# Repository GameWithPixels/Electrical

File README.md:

View this project on [CADLAB.io](https://cadlab.io/project/24232). 

# Electrical

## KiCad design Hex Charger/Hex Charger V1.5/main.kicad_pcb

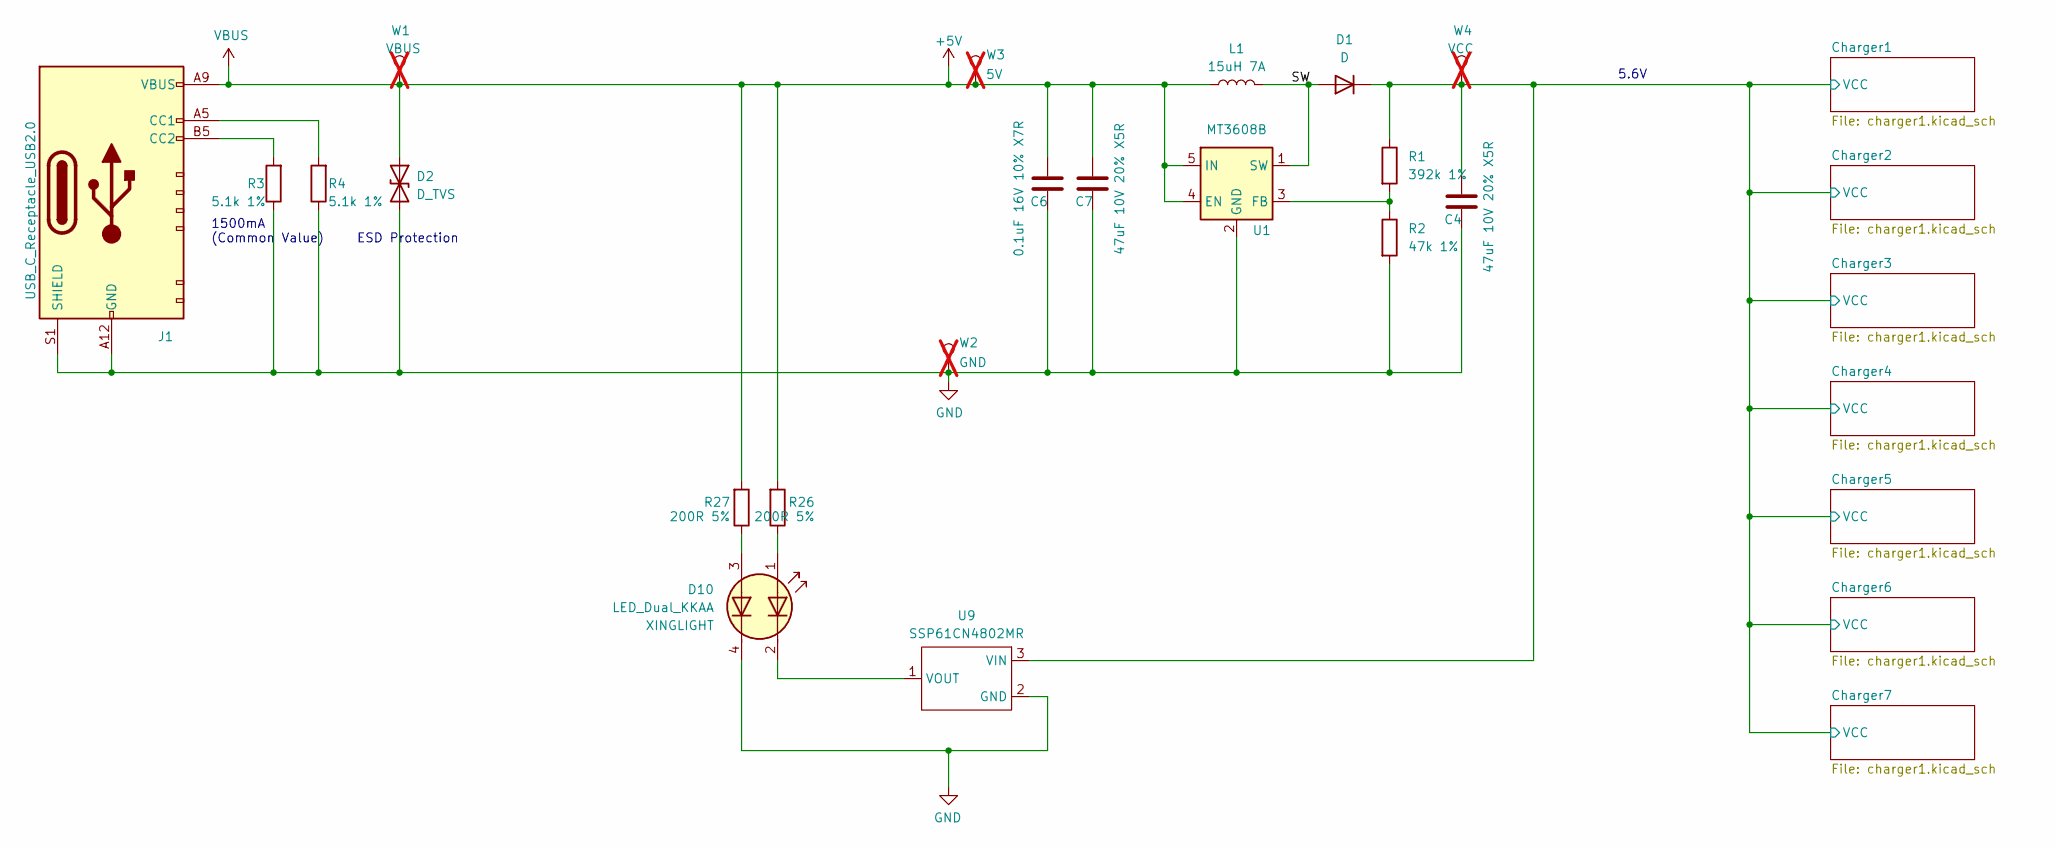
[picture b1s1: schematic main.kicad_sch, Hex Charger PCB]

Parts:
C4, C7: 47uF 10V 20% X5R; C_1206_3216Metric; Part Number CGA1206X5R476M100NT
C6: 0.1uF 16V 10% X7R; C_0603_1608Metric; Part Number CGA0603X7R104K500JT
D1: D; SMAF; Part Number SS54F; LCSC Part # C908671
D2: D_TVS; DFN; Part Number LXES1UTAA1-157; LCSC Part # C5210979
D10: LED_Dual_KKAA; XL-3210SURUGC; Part Number XL-3210SURUGC; LCSC Part # C965883
J1: USB_C_Receptacle_USB2.0; USB-C-SMD_10P-P1.00-L6.8-W8.9; Part Number TYPE-C-31-M-17; LCSC Part # C283540
L1: 15uH 7A; L_Sunlord_MWSA1005S; Part Number MS1050-150M; LCSC Part # C18337490
R1: 392k 1%; R_0402_1005Metric; Part Number 0402WGF3923TCE
R2: 47k 1%; R_0402_1005Metric; Part Number 0402WGF4702TCE
R3, R4: 5.1k 1%; R_0402_1005Metric; Part Number 0402WGF5101TCE; LCSC Part # C25905
R26, R27: 200R 5%; R_0402_1005Metric; Part Number 0402WGF2000TCE; LCSC Part # C25087
U1: MT3608B; SOT-23-6; Part Number MT3608B; LCSC Part # C19189893
U9: SSP61CN4802MR; SOT-23; Part Number HT7050S; LCSC Part # C2842953
W1: VBUS; TestPoint_1.5x1.5_Drill0.9mm; not fitted
W2: GND; TestPoint_1.5x1.5_Drill0.9mm; not fitted
W3: 5V; TestPoint_1.5x1.5_Drill0.9mm; not fitted
W4: VCC; TestPoint_1.5x1.5_Drill0.9mm; not fitted

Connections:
+5V: C6.1, C7.1, D2.1 (A1), J1.A9 (VBUS), J1.B9 (VBUS), L1.1, R26.2, R27.2, U1.4 (EN), U1.5 (IN), W1.1, W3.1
/Charger1/VCC: C4.1, D1.1 (K), R1.1, U9.3 (VIN), W4.1; also elsewhere on the board
/SW: D1.2 (A), L1.2, U1.1 (SW)
GND: C4.2, C6.2, C7.2, D2.2 (A2), D10.4 (K2), J1.A12 (GND), J1.B12 (GND), J1.S1 (SHIELD), R2.2, R3.1, R4.1, U1.2 (GND), U9.2 (GND), W2.1; also elsewhere on the board
unnamed: D10.1 (A1), R26.1
unnamed: D10.3 (A2), R27.1
unnamed: D10.2 (K1), U9.1 (VOUT)
unnamed: J1.A5 (CC1), R4.2
unnamed: J1.B5 (CC2), R3.2
unnamed: R1.2, R2.1, U1.3 (FB)

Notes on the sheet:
1500mA (Common Value)
5.6V
ESD Protection

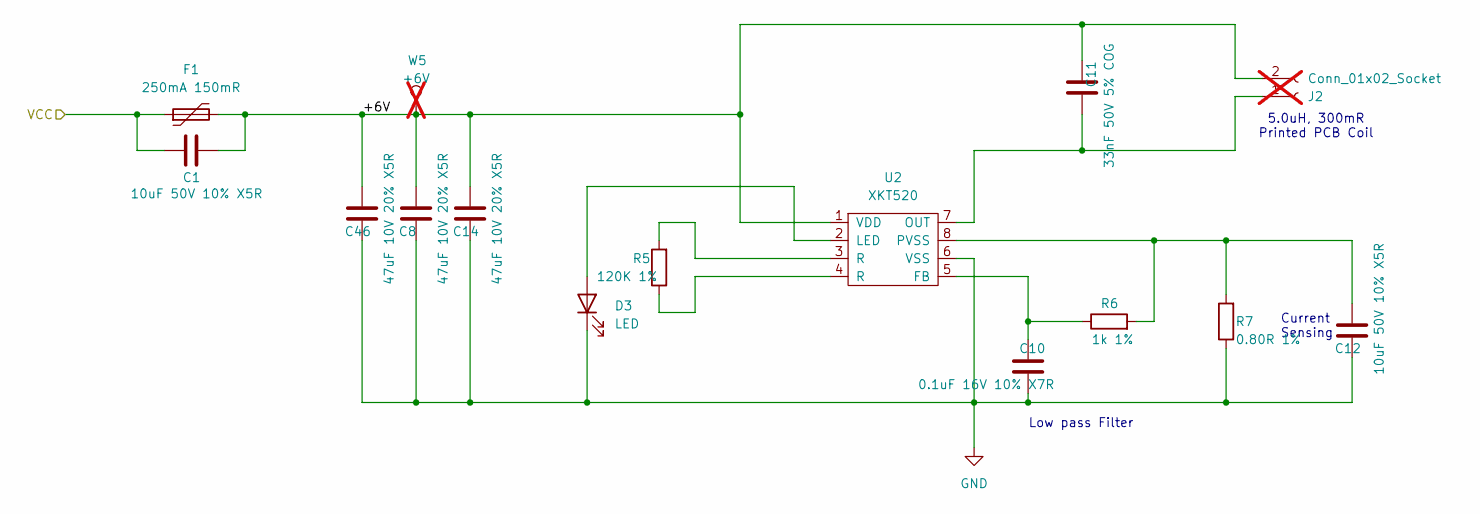
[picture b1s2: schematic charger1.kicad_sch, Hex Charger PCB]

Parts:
C1, C12: 10uF 50V 10% X5R; C_0805_2012Metric; Part Number CGA0805X5R106K250MT
C8, C14, C46: 47uF 10V 20% X5R; C_1206_3216Metric; Part Number CGA1206X5R476M100NT
C10: 0.1uF 16V 10% X7R; C_0603_1608Metric; Part Number CGA0603X7R104K500JT
C11: 33nF 50V 5% COG; C_1206_3216Metric; Part Number GRM3195C1H333JA01D; LCSC Part # C97930
D3: LED; LED_0603_1608Metric; Part Number LTST-C191KRKT; LCSC Part # C125099
F1: 250mA 150mR; Fuse_1206_3216Metric; Part Number BSMD1206-025-33V; LCSC Part # C2977524
J2: Conn_01x02_Socket; COIL_25_6_11T_0750_0255; not fitted
R5: 120K 1%; R_0402_1005Metric; Part Number 0402WGF1203TCE; LCSC Part # C25750
R6: 1k 1%; R_0402_1005Metric; Part Number 0402WGF1001TCE; LCSC Part # C11702
R7: 0.80R 1%; R_1206_3216Metric; Part Number 1206W4F800LT5E
U2: XKT520; SOIC-8_3.9x4.9mm_P1.27mm; Part Number 520
W5: +6V; TestPoint_1.5x1.5_Drill0.9mm; not fitted

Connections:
/Charger1/+6V: C1.1, C8.1, C11.2, C14.1, C46.1, F1.2, J2.2, U2.1 (VDD), W5.1
/Charger1/VCC: C1.2, F1.1; also elsewhere on the board
GND: C8.2, C10.1, C12.2, C14.2, C46.2, D3.1 (K), R7.1, U2.6 (VSS); also elsewhere on the board
unnamed: D3.2 (A), U2.2 (LED)
unnamed: C11.1, J2.1, U2.7 (OUT)
unnamed: R5.1, U2.4 (R)
unnamed: R5.2, U2.3 (R)
unnamed: C10.2, R6.1, U2.5 (FB)
unnamed: C12.1, R6.2, R7.2, U2.8 (PVSS)

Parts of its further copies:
C2, C3, C5, C17, C26, C27, C32, C37, C42, C43, C44, C45: 10uF 50V 10% X5R; C_0805_2012Metric; Part Number CGA0805X5R106K250MT
C13, C18, C19, C21, C28, C33, C34, C38, C47, C48, C49, C50, C51, C52, C53, C55, C57, C59: 47uF 10V 20% X5R; C_1206_3216Metric; Part Number CGA1206X5R476M100NT
C15, C22, C23, C30, C35, C40: 0.1uF 16V 10% X7R; C_0603_1608Metric; Part Number CGA0603X7R104K500JT
C16, C24, C25, C31, C36, C41: 33nF 50V 5% COG; C_1206_3216Metric; Part Number GRM3195C1H333JA01D; LCSC Part # C97930
D4, D5, D6, D7, D8, D9: LED; LED_0603_1608Metric; Part Number LTST-C191KRKT; LCSC Part # C125099
F2, F3, F4, F5, F6, F7: 250mA 150mR; Fuse_1206_3216Metric; Part Number BSMD1206-025-33V; LCSC Part # C2977524
J3, J4, J5, J6, J7, J8: Conn_01x02_Socket; COIL_25_6_11T_0750_0255; not fitted
R8, R11, R12, R17, R20, R23: 120K 1%; R_0402_1005Metric; Part Number 0402WGF1203TCE; LCSC Part # C25750
R9, R13, R14, R18, R21, R24: 1k 1%; R_0402_1005Metric; Part Number 0402WGF1001TCE; LCSC Part # C11702
R10, R15, R16, R19, R22, R25: 0.80R 1%; R_1206_3216Metric; Part Number 1206W4F800LT5E
U3, U4, U5, U6, U7, U8: XKT520; SOIC-8_3.9x4.9mm_P1.27mm; Part Number 520
W6, W7, W8, W9, W10, W11: +6V; TestPoint_1.5x1.5_Drill0.9mm; not fitted

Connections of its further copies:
/Charger1/VCC: C2.2, C3.2, C5.2, C43.2, C44.2, C45.2, F2.1, F3.1, F4.1, F5.1, F6.1, F7.1; also elsewhere on the board
/Charger2/+6V: C2.1, C13.1, C16.2, C21.1, C47.1, F2.2, J3.2, U3.1 (VDD), W6.1
/Charger3/+6V: C3.1, C18.1, C24.2, C34.1, C48.1, F3.2, J4.2, U4.1 (VDD), W7.1
/Charger4/+6V: C5.1, C19.1, C25.2, C49.1, C53.1, F4.2, J5.2, U5.1 (VDD), W8.1
/Charger5/+6V: C28.1, C31.2, C43.1, C50.1, C55.1, F5.2, J6.2, U6.1 (VDD), W9.1
/Charger6/+6V: C33.1, C36.2, C44.1, C51.1, C57.1, F6.2, J7.2, U7.1 (VDD), W10.1
/Charger7/+6V: C38.1, C41.2, C45.1, C52.1, C59.1, F7.2, J8.2, U8.1 (VDD), W11.1
GND: C13.2, C15.1, C17.2, C18.2, C19.2, C21.2, C22.1, C23.1, C26.2, C27.2, C28.2, C30.1, C32.2, C33.2, C34.2, C35.1, C37.2, C38.2, C40.1, C42.2, C47.2, C48.2, C49.2, C50.2, C51.2, C52.2, C53.2, C55.2, C57.2, C59.2, D4.1 (K), D5.1 (K), D6.1 (K), D7.1 (K), D8.1 (K), D9.1 (K), R10.1, R15.1, R16.1, R19.1, R22.1, R25.1, U3.6 (VSS), U4.6 (VSS), U5.6 (VSS), U6.6 (VSS), U7.6 (VSS), U8.6 (VSS); also elsewhere on the board
unnamed: D4.2 (A), U3.2 (LED)
unnamed: D5.2 (A), U4.2 (LED)
unnamed: D6.2 (A), U5.2 (LED)
unnamed: D7.2 (A), U6.2 (LED)
unnamed: D8.2 (A), U7.2 (LED)
unnamed: D9.2 (A), U8.2 (LED)
unnamed: C16.1, J3.1, U3.7 (OUT)
unnamed: C24.1, J4.1, U4.7 (OUT)
unnamed: C25.1, J5.1, U5.7 (OUT)
unnamed: C31.1, J6.1, U6.7 (OUT)
unnamed: C36.1, J7.1, U7.7 (OUT)
unnamed: C41.1, J8.1, U8.7 (OUT)
unnamed: R8.1, U3.4 (R)
unnamed: R8.2, U3.3 (R)
unnamed: R11.1, U4.4 (R)
unnamed: R11.2, U4.3 (R)
unnamed: R12.1, U5.4 (R)
unnamed: R12.2, U5.3 (R)
unnamed: R17.1, U6.4 (R)
unnamed: R17.2, U6.3 (R)
unnamed: R20.1, U7.4 (R)
unnamed: R20.2, U7.3 (R)
unnamed: R23.1, U8.4 (R)
unnamed: R23.2, U8.3 (R)
unnamed: C15.2, R9.1, U3.5 (FB)
unnamed: C17.1, R9.2, R10.2, U3.8 (PVSS)
unnamed: C22.2, R13.1, U4.5 (FB)
unnamed: C26.1, R13.2, R15.2, U4.8 (PVSS)
unnamed: C23.2, R14.1, U5.5 (FB)
unnamed: C27.1, R14.2, R16.2, U5.8 (PVSS)
unnamed: C30.2, R18.1, U6.5 (FB)
unnamed: C32.1, R18.2, R19.2, U6.8 (PVSS)
unnamed: C35.2, R21.1, U7.5 (FB)
unnamed: C37.1, R21.2, R22.2, U7.8 (PVSS)
unnamed: C40.2, R24.1, U8.5 (FB)
unnamed: C42.1, R24.2, R25.2, U8.8 (PVSS)

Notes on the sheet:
5.0uH, 300mR Printed PCB Coil
Current Sensing
Low pass Filter

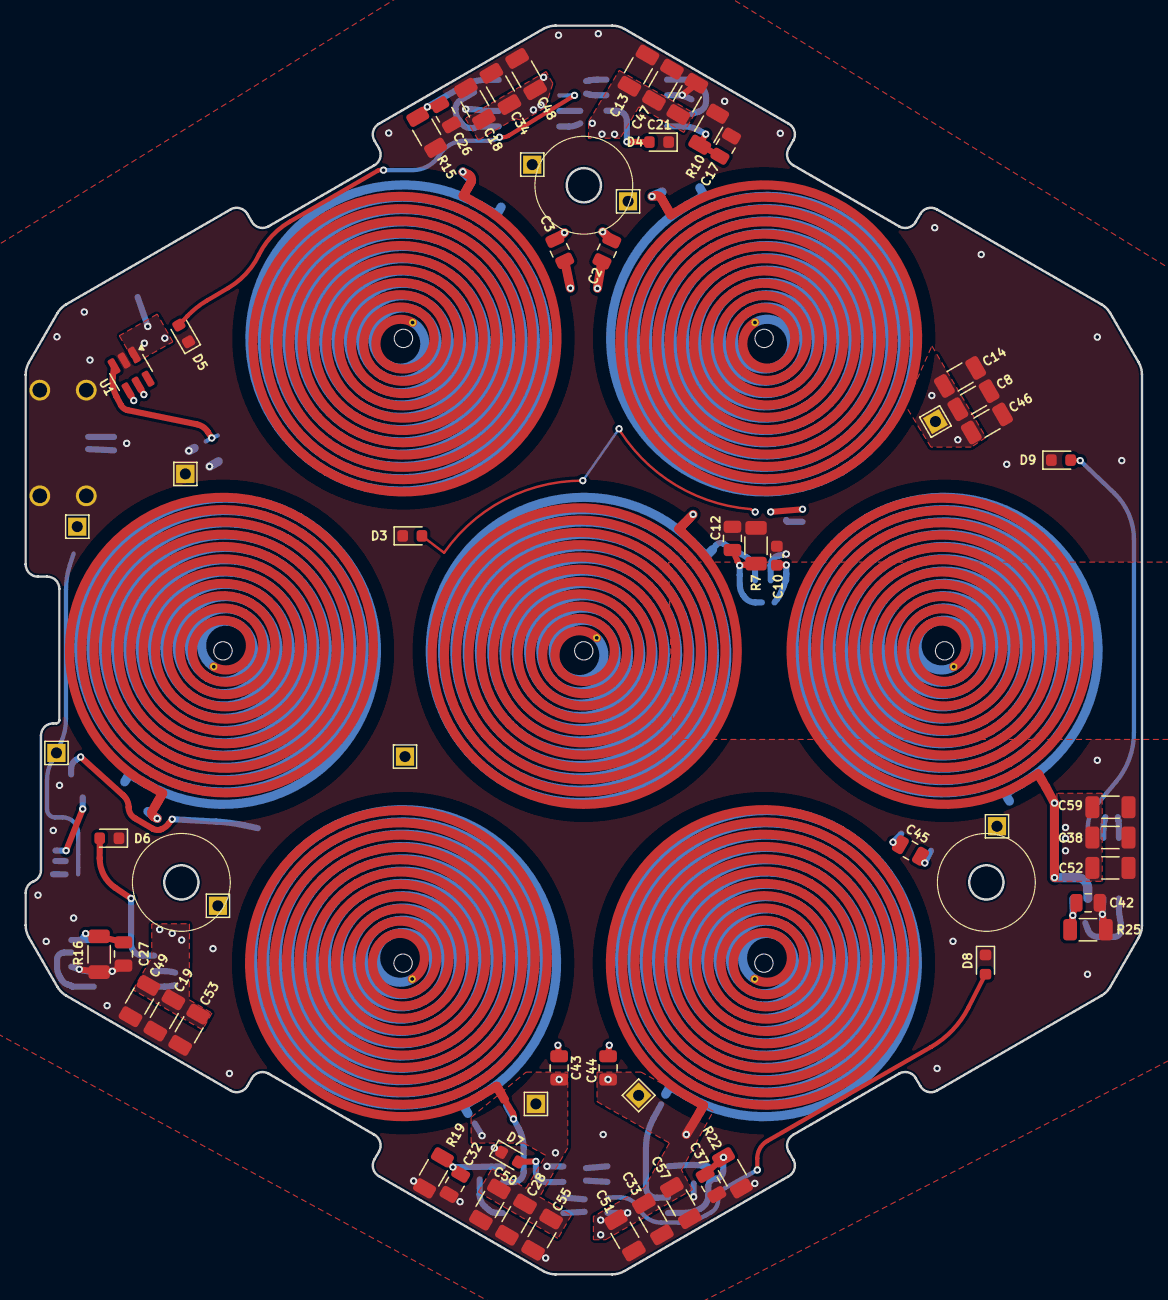
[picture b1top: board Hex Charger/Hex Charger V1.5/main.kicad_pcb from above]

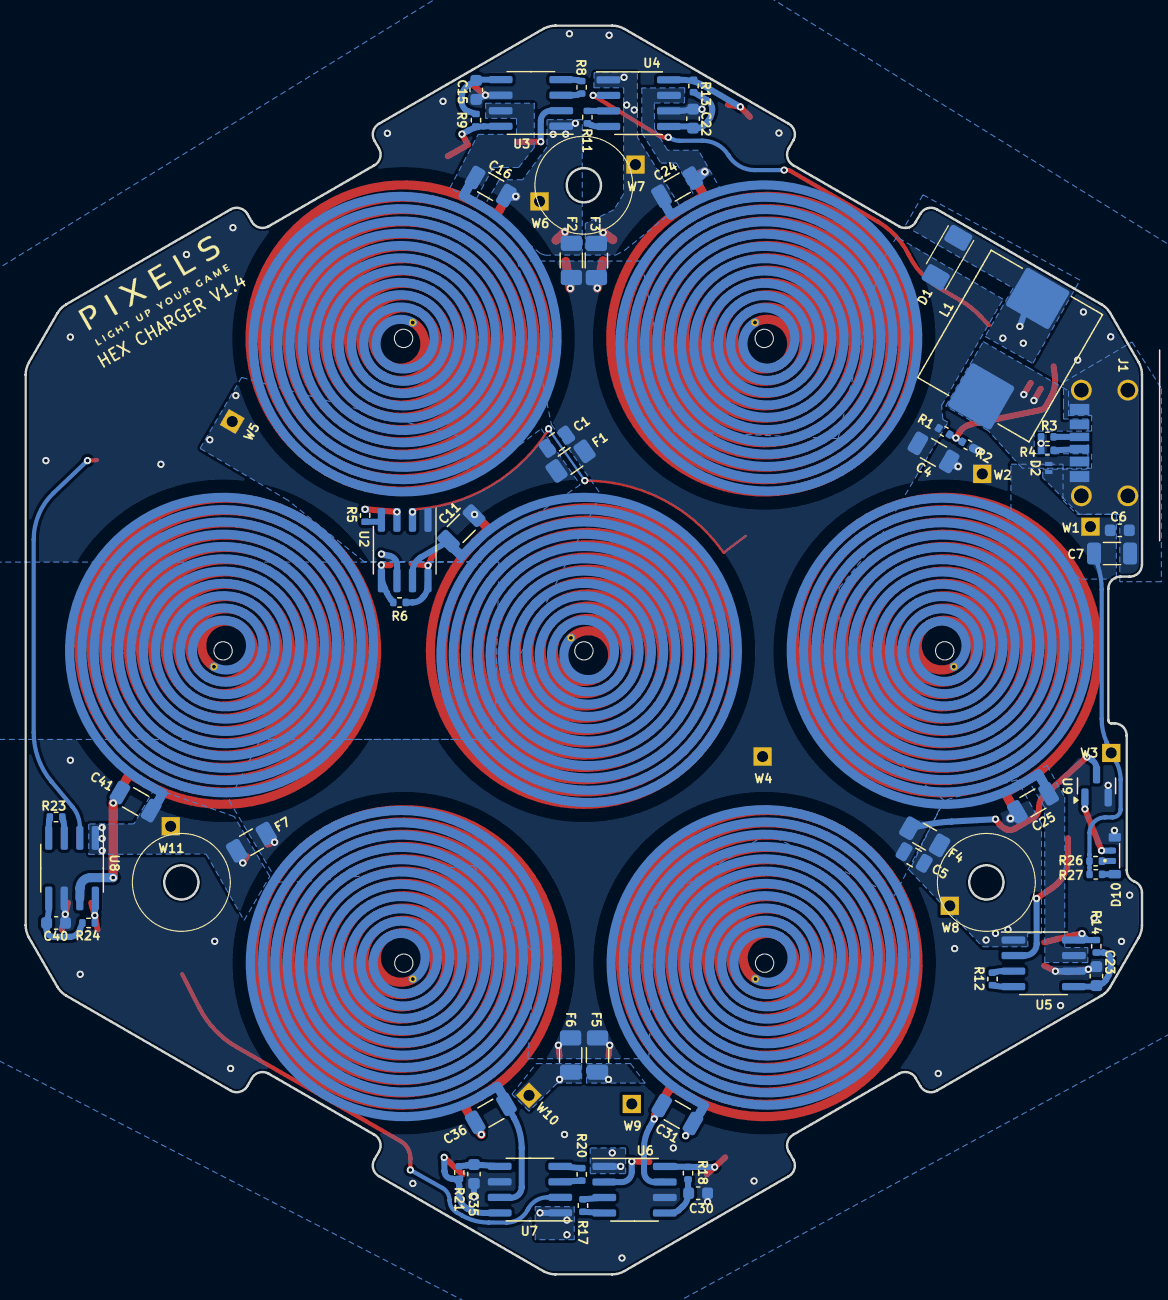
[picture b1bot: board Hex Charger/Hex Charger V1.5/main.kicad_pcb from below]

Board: 2 copper layers, 91.3 x 102.1 mm, 125 parts (62 on the bottom side), 59 nets.

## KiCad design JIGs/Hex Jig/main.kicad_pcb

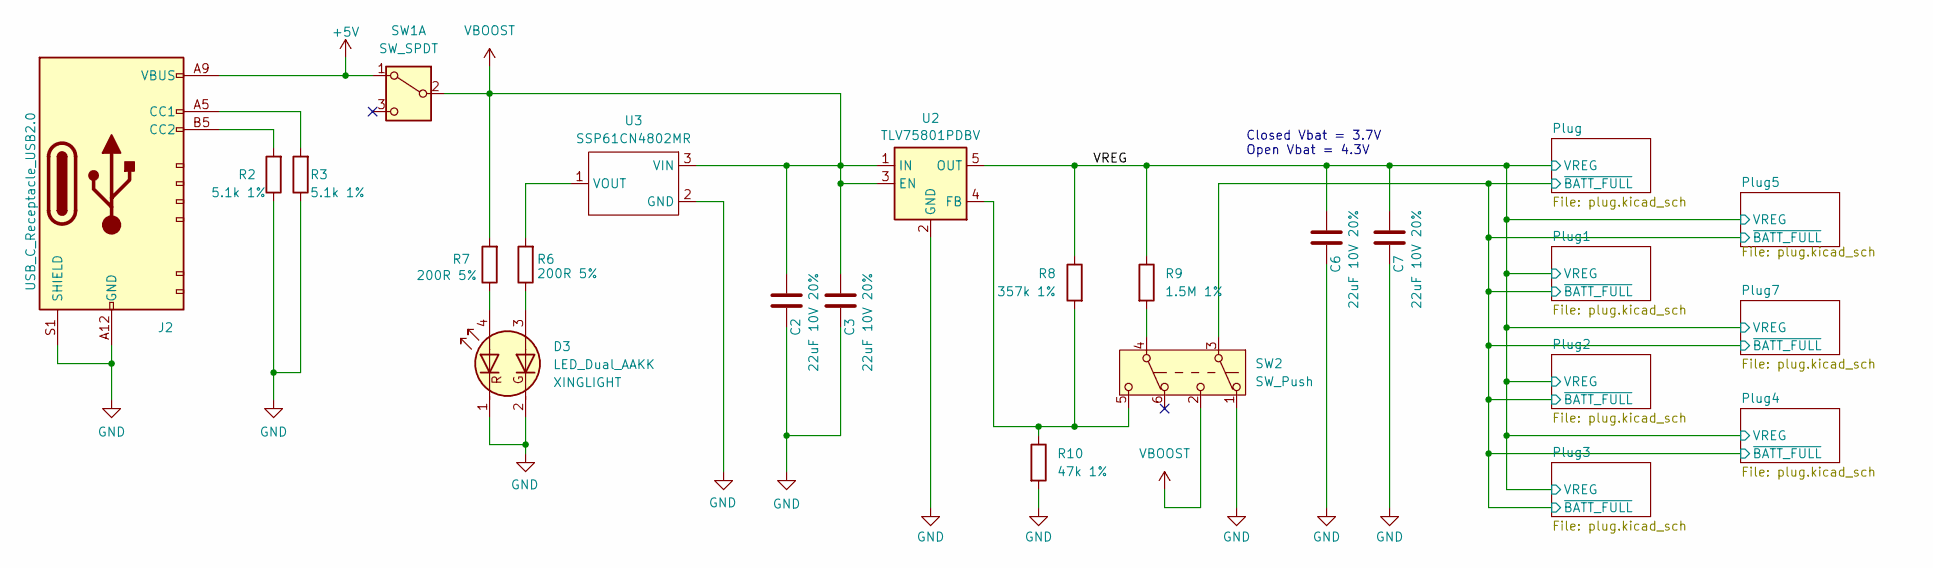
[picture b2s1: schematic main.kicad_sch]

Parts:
C2, C3, C6, C7: 22uF 10V 20%; C_0805_2012Metric; Manufacturer Part Number GRM21BR61A226ME51L
D3: LED_Dual_AAKK; XL-1615SURUGC; Part Number XL-1615SURUGC
J2: USB_C_Receptacle_USB2.0; USB-C-SMD_10P-P1.00-L6.8-W8.9; Part Number TYPE-C-31-M-17; LCSC Part Number C283540
R2, R3: 5.1k 1%; R_0402_1005Metric; Part Number 0402WGF5101TCE; LCSC Part Number C25905
R6, R7: 200R 5%; R_0402_1005Metric; Part Number 0402WGF2000TCE; LCSC Part # C25087
R8: 357k 1%; R_0402_1005Metric; Part Number 0402WGF3573TCE
R9: 1.5M 1%; R_0402_1005Metric; Part Number 0402WGF1504TCE
R10: 47k 1%; R_0402_1005Metric; Part Number 0402WGF4702TCE; LCSC Part Number C25819
SW1: SW_SPDT; MST22D18G2_125; Part Number MST22D18G2 125
SW2: SW_Push; PS-8055SVA-6PNA; Part Number PS-8055SVA-6PNA
U2: TLV75801PDBV; SOT-23-5; Part Number TLV75801PDBVR; LCSC Part Number C2877852
U3: SSP61CN4802MR; SOT-23; Part Number HT7050S; LCSC Part # C2842953

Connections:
+5V: J2.A9 (VBUS), J2.B9 (VBUS), SW1.1 (A)
/Plug/~BATT_FULL: SW2.3 (B); also elsewhere on the board
/VREG: C6.1, C7.1, R8.1, R9.1, U2.5 (OUT); also elsewhere on the board
GND: C2.2, C3.2, C6.2, C7.2, D3.1 (K1), D3.2 (K2), J2.A12 (GND), J2.B12 (GND), J2.S1 (SHIELD), R2.1, R3.1, R10.2, SW2.1 (A), U2.2 (GND), U3.2 (GND); also elsewhere on the board
unnamed: D3.4 (A1), R7.1
unnamed: D3.3 (A2), R6.1
unnamed: J2.A5 (CC1), R3.2
unnamed: J2.B5 (CC2), R2.2
unnamed: R9.2, SW2.4 (B)
unnamed: R8.2, R10.1, SW2.5 (C), U2.4 (FB)
unnamed: R6.2, U3.1 (VOUT)
VBOOST: C2.1, C3.1, R7.2, SW1.2 (B), SW2.2 (C), U2.1 (IN), U2.3 (EN), U3.3 (VIN)

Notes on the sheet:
Closed Vbat = 3.7V Open Vbat = 4.3V

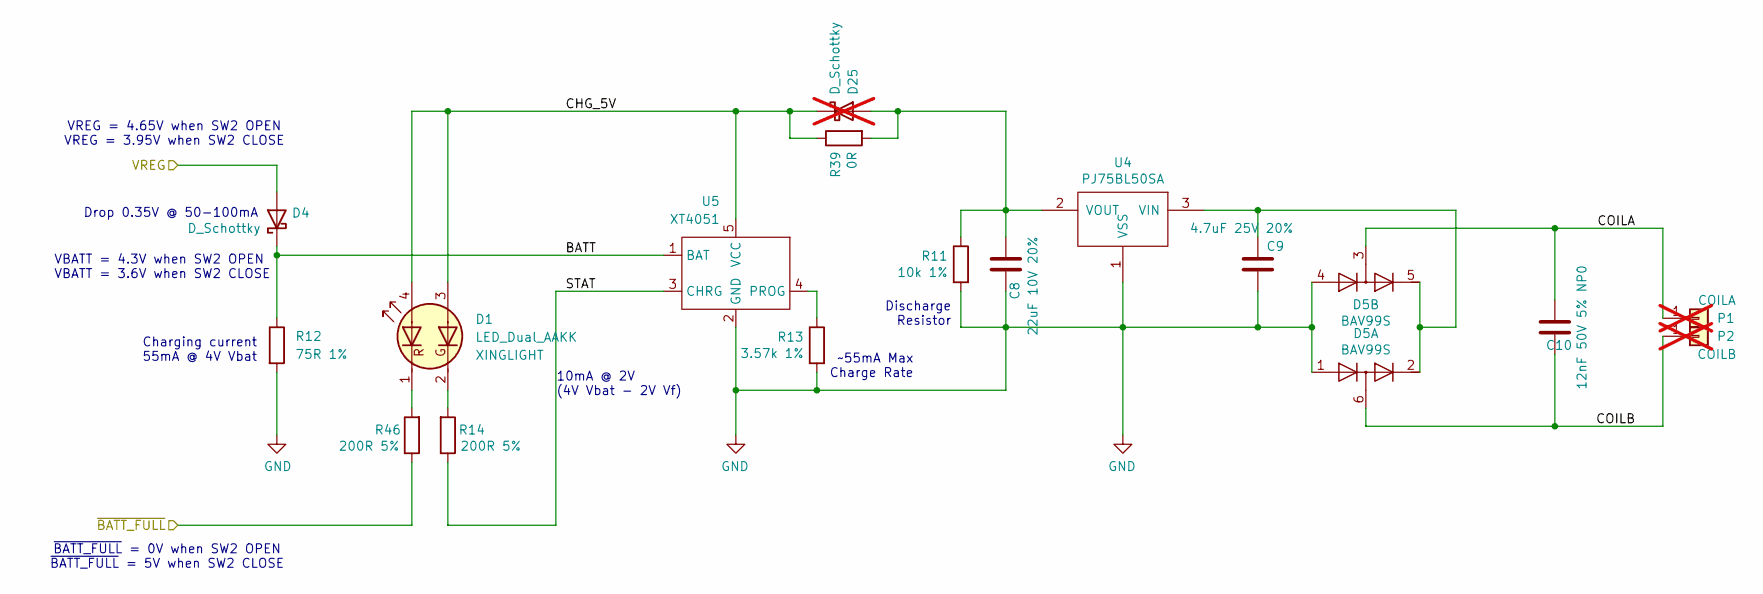
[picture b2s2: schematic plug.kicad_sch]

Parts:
C8: 22uF 10V 20%; C_0805_2012Metric; Manufacturer Part Number GRM21BR61A226ME51L
C9: 4.7uF 25V 20%; C_0402_1005Metric; Part Number CGA0402X5R475M250GT; LCSC Part # C6119795
C10: 12nF 50V 5% NP0; C_0805_2012Metric; Part Number GRM2195C1H123JA01D
D1: LED_Dual_AAKK; XL-1615SURUGC; Part Number XL-1615SURUGC
D4: D_Schottky; D_SOD-523; Part Number RB521S30T1G; LCSC Part Number C145179
D5: BAV99S; SOT-363_SC-70-6; Part Number BAV99S,115; LCSC Part # C96225
D25: D_Schottky; D_SOD-523; Part Number RB521S30T1G; LCSC Part Number C145179; not fitted
P1: COILA; TestPoint_THTPad_D1.5mm_Drill0.7mm; not fitted
P2: COILB; TestPoint_THTPad_D1.5mm_Drill0.7mm; not fitted
R11: 10k 1%; R_0402_1005Metric; Part Number 0402WGF1002TCE; LCSC Part # C473048
R12: 75R 1%; R_1210_3225Metric; Part Number RC1210JR-0782RL; LCSC Part Number C728413
R13: 3.57k 1%; R_0402_1005Metric; Part Number 0402WGF3571TCE
R14, R46: 200R 5%; R_0402_1005Metric; Part Number 0402WGF2000TCE; LCSC Part # C25087
R39: 0R; R_0402_1005Metric; Part Number 0402WGF0000TCE
U4: PJ75BL50SA; SOT-23; Part Number PJ75BL50SA
U5: XT4051; SOT-553; Part Number XT4051K421KR-G; LCSC Part # C219186

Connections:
/Plug/BATT: D4.1 (K), R12.1, U5.1 (BAT)
/Plug/CHG_5V: D1.3 (A2), D1.4 (A1), D25.1 (K), R39.1, U5.5 (VCC)
/Plug/COILA: C10.1, D5.3 (K1A2), P1.1
/Plug/COILB: C10.2, D5.6 (K3A4), P2.1
/Plug/STAT: R14.1, U5.3 (CHRG)
/Plug/~BATT_FULL: R46.1; also elsewhere on the board
/VREG: D4.2 (A); also elsewhere on the board
GND: C8.2, C9.2, D5.1 (A1), D5.4 (A3), R11.2, R12.2, R13.2, U4.1 (VSS), U5.2 (GND); also elsewhere on the board
unnamed: D1.1 (K1), R46.2
unnamed: D1.2 (K2), R14.2
unnamed: C9.1, D5.2 (K2), D5.5 (K4), U4.3 (VIN)
unnamed: C8.1, D25.2 (A), R11.1, R39.2, U4.2 (VOUT)
unnamed: R13.1, U5.4 (PROG)

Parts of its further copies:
C11, C14, C17, C20, C23, C26: 22uF 10V 20%; C_0805_2012Metric; Manufacturer Part Number GRM21BR61A226ME51L
C12, C15, C18, C21, C24, C27: 4.7uF 25V 20%; C_0402_1005Metric; Part Number CGA0402X5R475M250GT; LCSC Part # C6119795
C13, C16, C19, C22, C25, C28: 12nF 50V 5% NP0; C_0805_2012Metric; Part Number GRM2195C1H123JA01D
D6, D9, D12, D15, D18, D21: LED_Dual_AAKK; XL-1615SURUGC; Part Number XL-1615SURUGC
D7, D10, D13, D16, D19, D22: D_Schottky; D_SOD-523; Part Number RB521S30T1G; LCSC Part Number C145179
D8, D11, D14, D17, D20, D23: BAV99S; SOT-363_SC-70-6; Part Number BAV99S,115; LCSC Part # C96225
D26, D27, D28, D29, D30, D31: D_Schottky; D_SOD-523; Part Number RB521S30T1G; LCSC Part Number C145179; not fitted
P3, P5, P7, P9, P11, P13: COILA; TestPoint_THTPad_D1.5mm_Drill0.7mm; not fitted
P4, P6, P8, P10, P12, P14: COILB; TestPoint_THTPad_D1.5mm_Drill0.7mm; not fitted
R15, R19, R23, R27, R31, R35: 10k 1%; R_0402_1005Metric; Part Number 0402WGF1002TCE; LCSC Part # C473048
R16, R20, R24, R28, R32, R36: 75R 1%; R_1210_3225Metric; Part Number RC1210JR-0782RL; LCSC Part Number C728413
R17, R21, R25, R29, R33, R37: 3.57k 1%; R_0402_1005Metric; Part Number 0402WGF3571TCE
R18, R22, R26, R30, R34, R38, R47, R48, R49, R50, R51, R52: 200R 5%; R_0402_1005Metric; Part Number 0402WGF2000TCE; LCSC Part # C25087
R40, R41, R42, R43, R44, R45: 0R; R_0402_1005Metric; Part Number 0402WGF0000TCE
U6, U8, U10, U12, U14, U16: PJ75BL50SA; SOT-23; Part Number PJ75BL50SA
U7, U9, U11, U13, U15, U17: XT4051; SOT-553; Part Number XT4051K421KR-G; LCSC Part # C219186

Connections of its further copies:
/Plug1/BATT: D7.1 (K), R16.1, U7.1 (BAT)
/Plug1/CHG_5V: D6.3 (A2), D6.4 (A1), D26.1 (K), R40.1, U7.5 (VCC)
/Plug1/COILA: C13.1, D8.3 (K1A2), P3.1
/Plug1/COILB: C13.2, D8.6 (K3A4), P4.1
/Plug1/STAT: R18.1, U7.3 (CHRG)
/Plug2/BATT: D10.1 (K), R20.1, U9.1 (BAT)
/Plug2/CHG_5V: D9.3 (A2), D9.4 (A1), D27.1 (K), R41.1, U9.5 (VCC)
/Plug2/COILA: C16.1, D11.3 (K1A2), P5.1
/Plug2/COILB: C16.2, D11.6 (K3A4), P6.1
/Plug2/STAT: R22.1, U9.3 (CHRG)
/Plug3/BATT: D13.1 (K), R24.1, U11.1 (BAT)
/Plug3/CHG_5V: D12.3 (A2), D12.4 (A1), D28.1 (K), R42.1, U11.5 (VCC)
/Plug3/COILA: C19.1, D14.3 (K1A2), P7.1
/Plug3/COILB: C19.2, D14.6 (K3A4), P8.1
/Plug3/STAT: R26.1, U11.3 (CHRG)
/Plug4/BATT: D22.1 (K), R36.1, U17.1 (BAT)
/Plug4/CHG_5V: D21.3 (A2), D21.4 (A1), D31.1 (K), R45.1, U17.5 (VCC)
/Plug4/COILA: C28.1, D23.3 (K1A2), P13.1
/Plug4/COILB: C28.2, D23.6 (K3A4), P14.1
/Plug4/STAT: R38.1, U17.3 (CHRG)
/Plug5/BATT: D16.1 (K), R28.1, U13.1 (BAT)
/Plug5/CHG_5V: D15.3 (A2), D15.4 (A1), D29.1 (K), R43.1, U13.5 (VCC)
/Plug5/COILA: C22.1, D17.3 (K1A2), P9.1
/Plug5/COILB: C22.2, D17.6 (K3A4), P10.1
/Plug5/STAT: R30.1, U13.3 (CHRG)
/Plug7/BATT: D19.1 (K), R32.1, U15.1 (BAT)
/Plug7/CHG_5V: D18.3 (A2), D18.4 (A1), D30.1 (K), R44.1, U15.5 (VCC)
/Plug7/COILA: C25.1, D20.3 (K1A2), P11.1
/Plug7/COILB: C25.2, D20.6 (K3A4), P12.1
/Plug7/STAT: R34.1, U15.3 (CHRG)
/Plug/~BATT_FULL: R47.1, R48.1, R49.1, R50.1, R51.1, R52.1; also elsewhere on the board
/VREG: D7.2 (A), D10.2 (A), D13.2 (A), D16.2 (A), D19.2 (A), D22.2 (A); also elsewhere on the board
GND: C11.2, C12.2, C14.2, C15.2, C17.2, C18.2, C20.2, C21.2, C23.2, C24.2, C26.2, C27.2, D8.1 (A1), D8.4 (A3), D11.1 (A1), D11.4 (A3), D14.1 (A1), D14.4 (A3), D17.1 (A1), D17.4 (A3), D20.1 (A1), D20.4 (A3), D23.1 (A1), D23.4 (A3), R15.2, R16.2, R17.2, R19.2, R20.2, R21.2, R23.2, R24.2, R25.2, R27.2, R28.2, R29.2, R31.2, R32.2, R33.2, R35.2, R36.2, R37.2, U6.1 (VSS), U7.2 (GND), U8.1 (VSS), U9.2 (GND), U10.1 (VSS), U11.2 (GND), U12.1 (VSS), U13.2 (GND), U14.1 (VSS), U15.2 (GND), U16.1 (VSS), U17.2 (GND); also elsewhere on the board
unnamed: D6.1 (K1), R47.2
unnamed: D6.2 (K2), R18.2
unnamed: C12.1, D8.2 (K2), D8.5 (K4), U6.3 (VIN)
unnamed: D9.1 (K1), R48.2
unnamed: D9.2 (K2), R22.2
unnamed: C15.1, D11.2 (K2), D11.5 (K4), U8.3 (VIN)
unnamed: D12.1 (K1), R49.2
unnamed: D12.2 (K2), R26.2
unnamed: C18.1, D14.2 (K2), D14.5 (K4), U10.3 (VIN)
unnamed: D15.1 (K1), R50.2
unnamed: D15.2 (K2), R30.2
unnamed: C21.1, D17.2 (K2), D17.5 (K4), U12.3 (VIN)
unnamed: D18.1 (K1), R51.2
unnamed: D18.2 (K2), R34.2
unnamed: C24.1, D20.2 (K2), D20.5 (K4), U14.3 (VIN)
unnamed: D21.1 (K1), R52.2
unnamed: D21.2 (K2), R38.2
unnamed: C27.1, D23.2 (K2), D23.5 (K4), U16.3 (VIN)
unnamed: C11.1, D26.2 (A), R15.1, R40.2, U6.2 (VOUT)
unnamed: C14.1, D27.2 (A), R19.1, R41.2, U8.2 (VOUT)
unnamed: C17.1, D28.2 (A), R23.1, R42.2, U10.2 (VOUT)
unnamed: C20.1, D29.2 (A), R27.1, R43.2, U12.2 (VOUT)
unnamed: C23.1, D30.2 (A), R31.1, R44.2, U14.2 (VOUT)
unnamed: C26.1, D31.2 (A), R35.1, R45.2, U16.2 (VOUT)
unnamed: R17.1, U7.4 (PROG)
unnamed: R21.1, U9.4 (PROG)
unnamed: R25.1, U11.4 (PROG)
unnamed: R29.1, U13.4 (PROG)
unnamed: R33.1, U15.4 (PROG)
unnamed: R37.1, U17.4 (PROG)

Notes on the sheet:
10mA @ 2V (4V Vbat - 2V Vf)
~{BATT_FULL} = 0V when SW2 OPEN ~{BATT_FULL} = 5V when SW2 CLOSE
Discharge Resistor
VBATT = 4.3V when SW2 OPEN VBATT = 3.6V when SW2 CLOSE
VREG = 4.65V when SW2 OPEN VREG = 3.95V when SW2 CLOSE
~55mA Max Charge Rate
Charging current 55mA @ 4V Vbat
Drop 0.35V @ 50-100mA

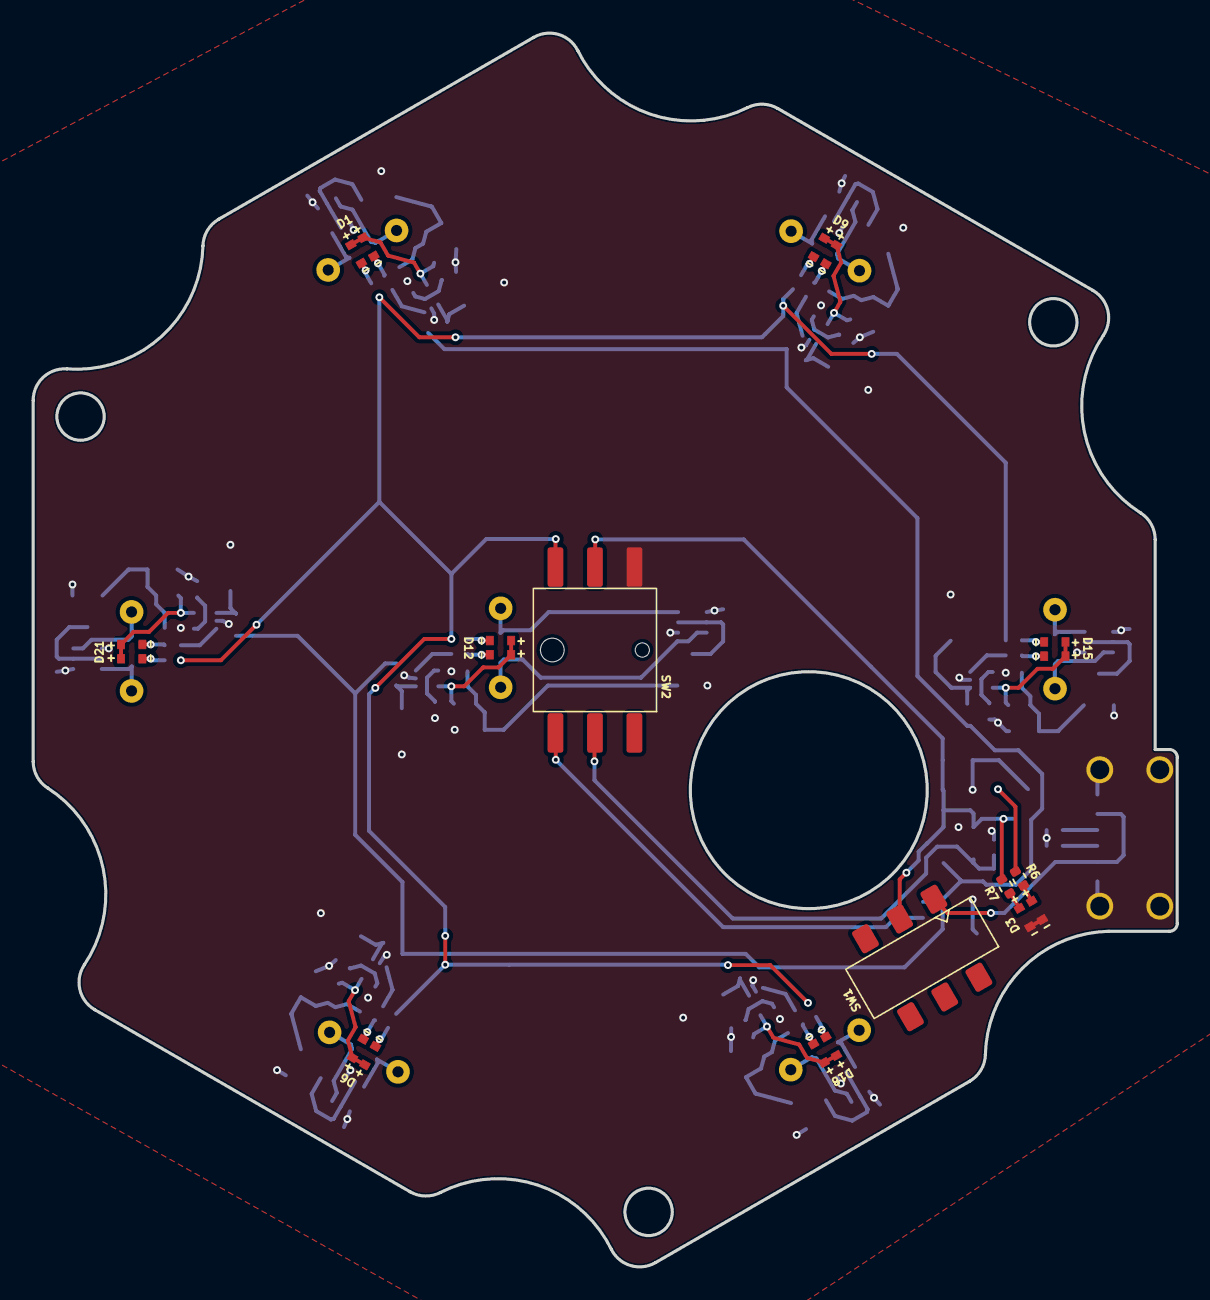
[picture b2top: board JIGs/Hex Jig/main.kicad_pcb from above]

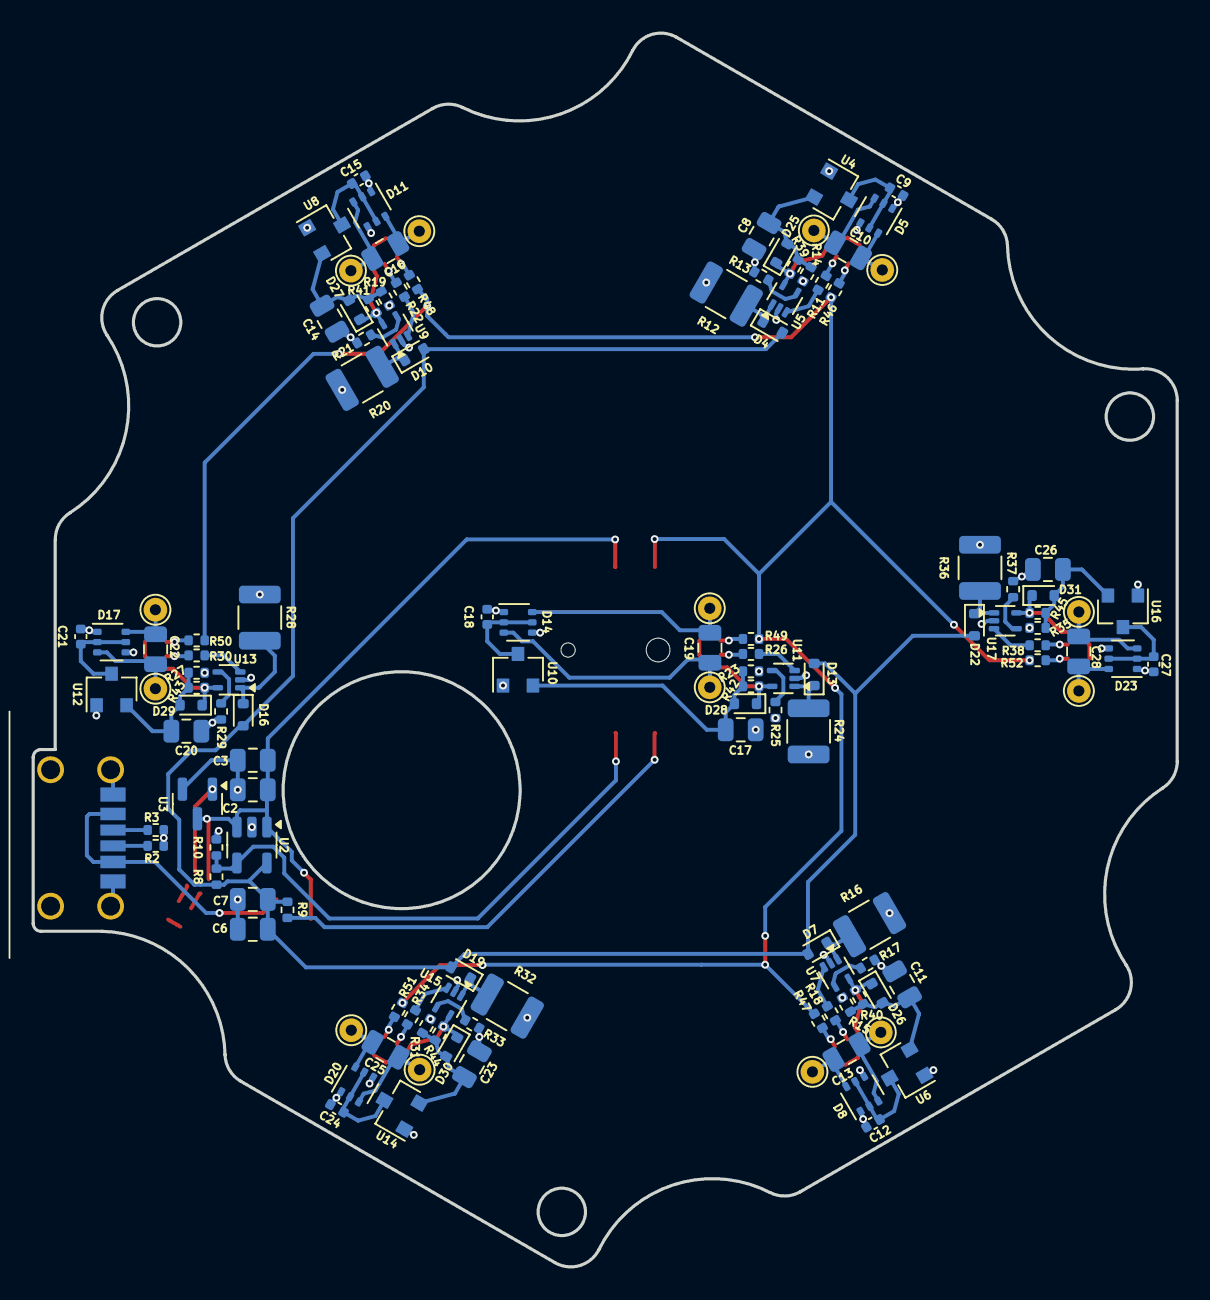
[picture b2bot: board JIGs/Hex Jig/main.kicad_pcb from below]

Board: 2 copper layers, 72.4 x 78.1 mm, 136 parts (124 on the bottom side), 82 nets.

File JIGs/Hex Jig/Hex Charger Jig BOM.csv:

"Reference","Value","Footprint","Qty","Manufacturer","Part Number"
"C2,C3,C6,C7,C8,C11,C14,C17,C20,C23,C26","22uF 10V 20%","Capacitor_SMD:C_0805_2012Metric","11","Murata","GRM21BR61A226ME51L"
"C9,C12,C15,C18,C21,C24,C27","4.7uF 25V 20%","Capacitor_SMD:C_0402_1005Metric","7","HRE","CGA0402X5R475M250GT"
"C10,C13,C16,C19,C22,C25,C28","12nF 50V 5% NP0","Capacitor_SMD:C_0805_2012Metric","7","Murata","GRM2195C1H123JA01D"
"D1,D3,D6,D9,D12,D15,D18,D21","LED_Dual_AAKK","Pixels-dice:XL-1615SURUGC","8","XINGLIGHT","XL-1615SURUGC"
"D4,D7,D10,D13,D16,D19,D22","D_Schottky","Diode_SMD:D_SOD-523","7","onsemi","RB521S30T1G"
"D5,D8,D11,D14,D17,D20,D23","BAV99S","Pixels-dice:SOT-363_SC-70-6","7","Nexperia","BAV99S,115"
"J2","USB_C_Receptacle_USB2.0","Pixels-dice:USB-C-SMD_10P-P1.00-L6.8-W8.9","1","Korean Hroparts Elec","TYPE-C-31-M-17"
"P1,P3,P5,P7,P9,P11,P13","COILA","TestPoint:TestPoint_THTPad_D1.5mm_Drill0.7mm","7","",""
"P2,P4,P6,P8,P10,P12,P14","COILB","TestPoint:TestPoint_THTPad_D1.5mm_Drill0.7mm","7","",""
"R2,R3","5.1k 1%","Resistor_SMD:R_0402_1005Metric","2","UNI-ROYAL(Uniroyal Elec)","0402WGF5101TCE"
"R6,R7,R14,R18,R22,R26,R30,R34,R38,R46,R47,R48,R49,R50,R51,R52","200R 5%","Resistor_SMD:R_0402_1005Metric","16","UNI-ROYAL(Uniroyal Elec)","0402WGF2000TCE"
"R8","357k 1%","Resistor_SMD:R_0402_1005Metric","1","UNI-ROYAL(Uniroyal Elec)"," 0402WGF3573TCE"
"R9","1.5M 1%","Resistor_SMD:R_0402_1005Metric","1","UNI-ROYAL(Uniroyal Elec)","0402WGF1504TCE"
"R10","47k 1%","Resistor_SMD:R_0402_1005Metric","1","UNI-ROYAL(Uniroyal Elec)","0402WGF4702TCE"
"R11,R15,R19,R23,R27,R31,R35","10k 1%","Resistor_SMD:R_0402_1005Metric","7","UNI-ROYAL(Uniroyal Elec)","0402WGF1002TCE"
"R12,R16,R20,R24,R28,R32,R36","75R 1%","Resistor_SMD:R_1210_3225Metric","7","YAGEO","RC1210JR-0782RL"
"R13,R17,R21,R25,R29,R33,R37","3.57k 1%","Resistor_SMD:R_0402_1005Metric","7","UNI-ROYAL(Uniroyal Elec)","0402WGF3571TCE"
"R39,R40,R41,R42,R43,R44,R45","0R","Resistor_SMD:R_0402_1005Metric","7","UNI-ROYAL(Uniroyal Elec)","0402WGF0000TCE"
"SW1","SW_SPDT","Pixels-dice:MST22D18G2_125","1","SHOU HAN","MST22D18G2 125"
"SW2","SW_Push","Pixels-dice:PS-8055SVA-6PNA","1","G-Switch","PS-8055SVA-6PNA"
"U2","TLV75801PDBV","Package_TO_SOT_SMD:SOT-23-5","1","Texas Instruments","TLV75801PDBVR"
"U3","SSP61CN4802MR","Package_TO_SOT_SMD:SOT-23","1","UMW(Youtai Semiconductor Co., Ltd.)","HT7050S"
"U4,U6,U8,U10,U12,U14,U16","PJ75BL50SA","Pixels-dice:SOT-23","7","PJSEMI","PJ75BL50SA"
"U5,U7,U9,U11,U13,U15,U17","XT4051","Package_TO_SOT_SMD:SOT-553","7","NATLINEAR","XT4051K421KR-G"
